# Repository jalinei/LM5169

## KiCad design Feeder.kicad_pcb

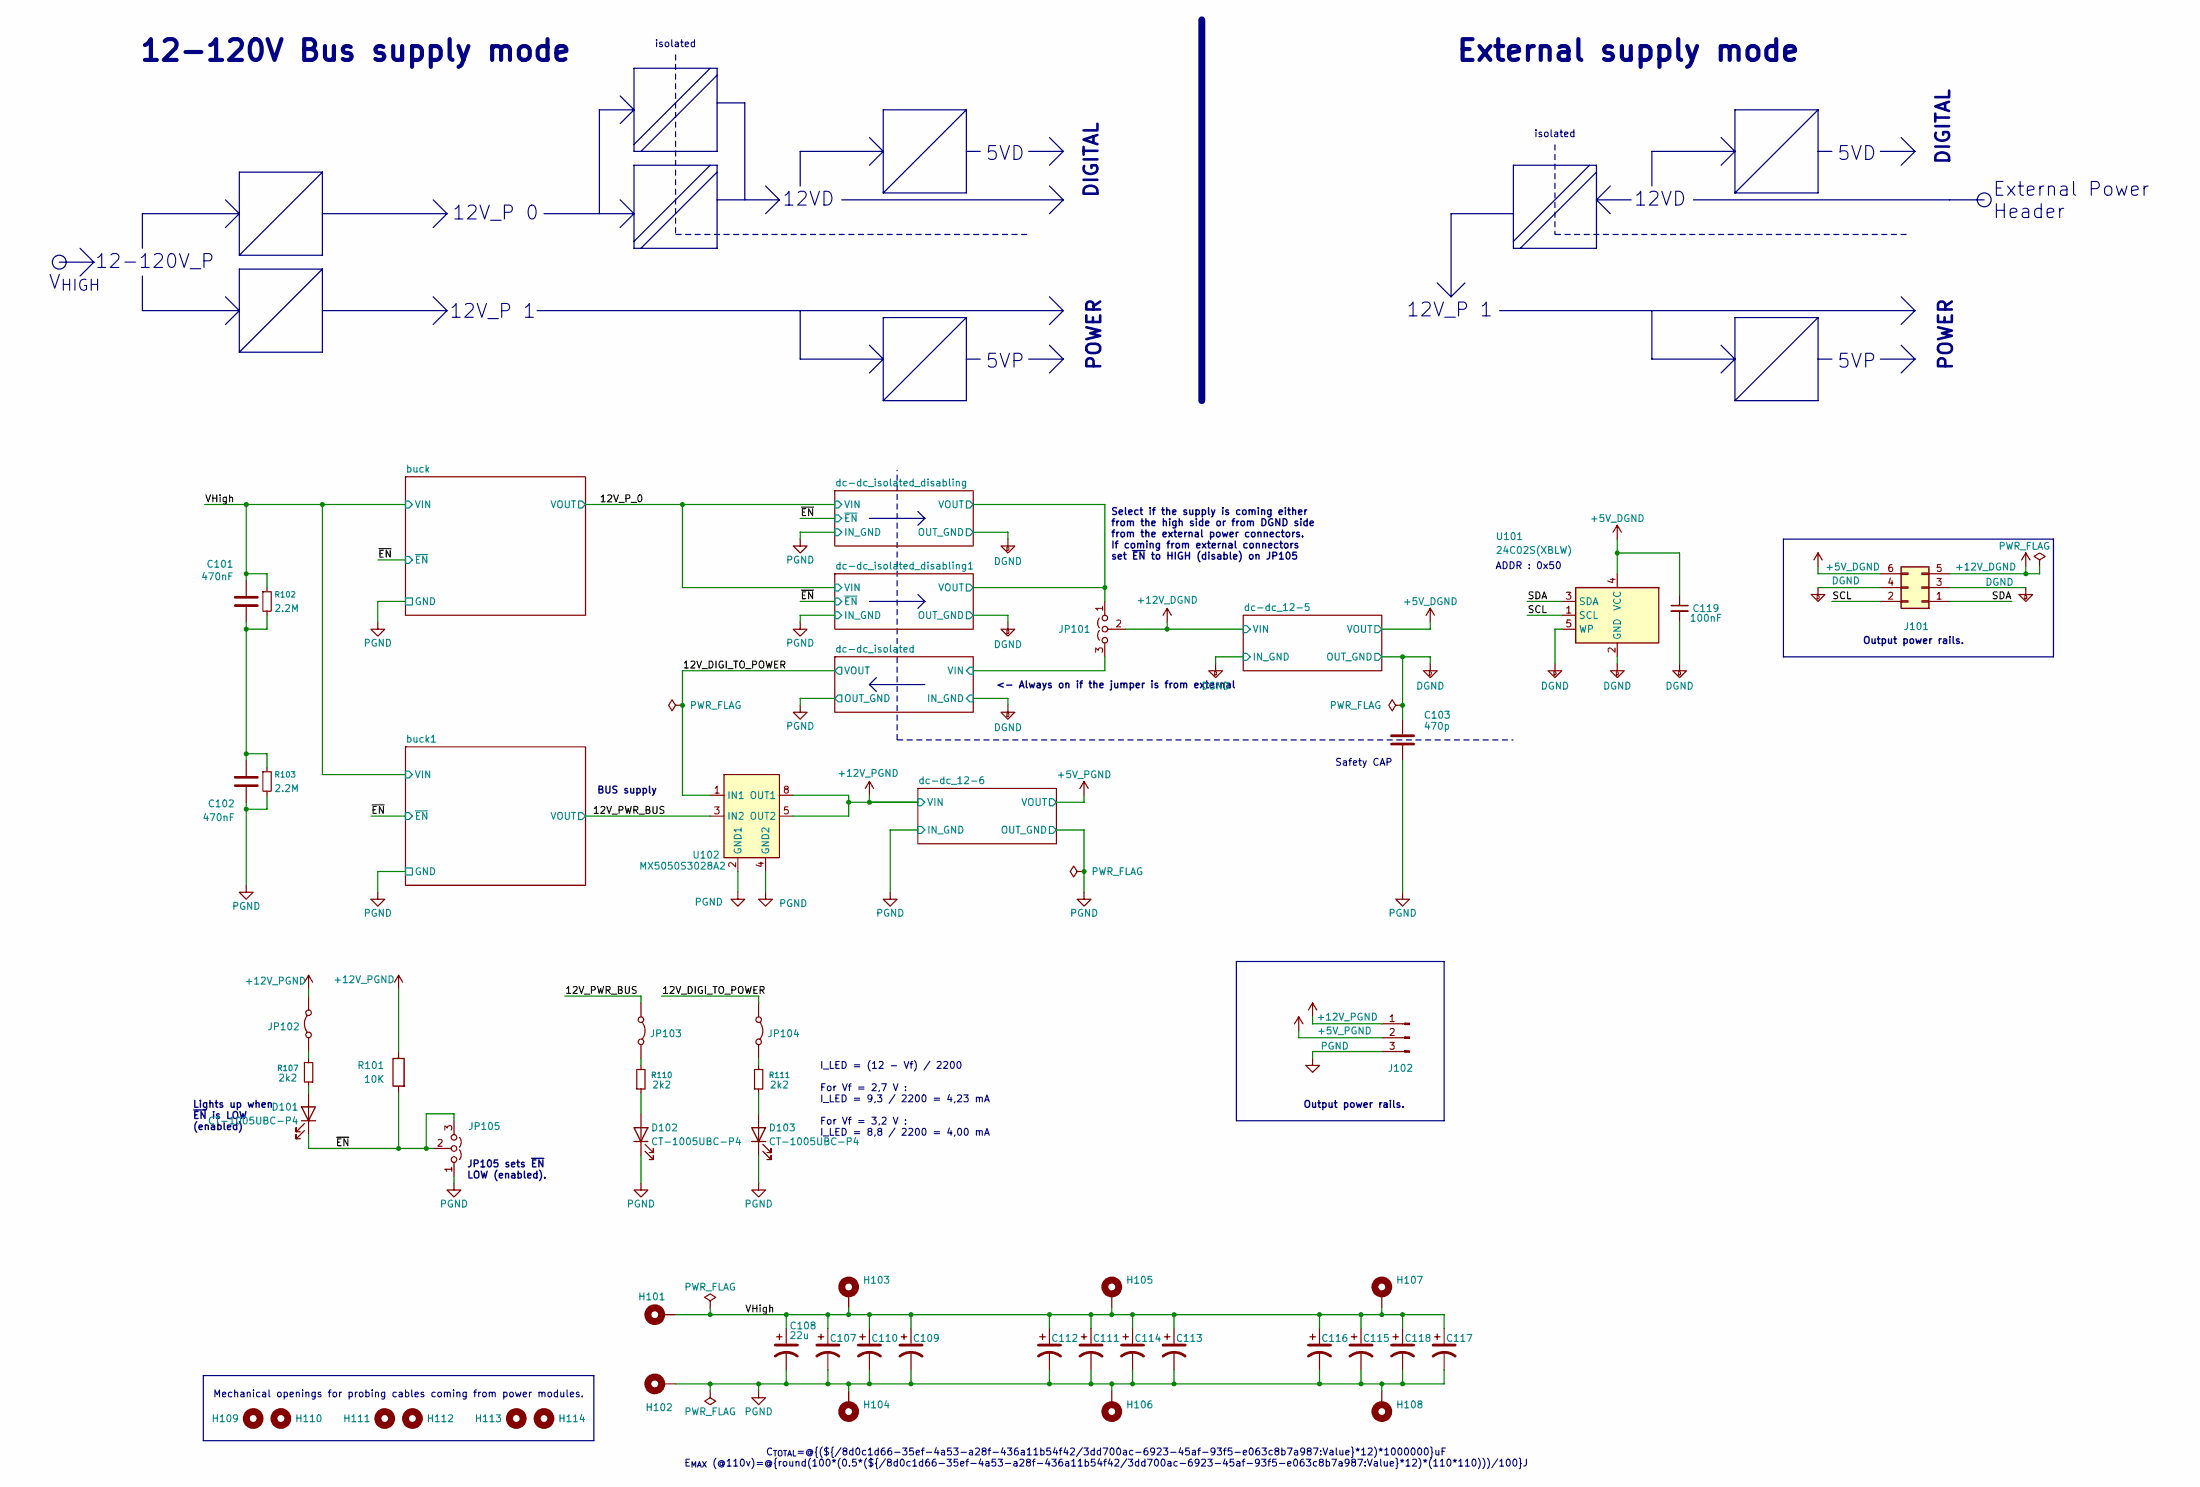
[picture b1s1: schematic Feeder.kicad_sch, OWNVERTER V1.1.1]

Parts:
C101, C102: 470nF; C_0805_2012Metric; LCSC C596323
C103: 470p; SAFETY_CAP_8.1x6mm; LCSC C20625786
C107, C108, C109, C110, C111, C112, C113, C114, C115, C116, C117, C118: 22u; CP_Elec_10x12.6; LCSC C487461
C119: 100nF; C_0603_1608Metric; LCSC C14663
D101, D102, D103: CT-1005UBC-P4; LED_0402_1005Metric; LCSC C52675962
H101, H102, H103, H104, H105, H106, H107, H108: MountingHole_Pad; MountingHole_3.2mm_M3_Pad_Via
H109, H110, H111, H112, H113, H114: MountingHole; Hole_signal_bottom_board_lookup
J101: PZ254V-22-06-A60-1500; PinHeader_2x03_P2.54mm_Vertical; LCSC C49056253
J102: PZ254V-21-03-A60-1500; PinHeader_1x03_P2.54mm_Vertical; LCSC C46971097
JP101, JP105: Jumper_3_Open; PinHeader_1x03_P2.54mm_Vertical
JP102, JP103, JP104: Jumper_2_Bridged; SolderJumper-2_P1.3mm_Bridged_RoundedPad1.0x1.5mm
R101: 10K; R_0603_1608Metric; LCSC C25804
R102, R103: 2.2M; R_0603_1608Metric; LCSC C22356574
R107, R110, R111: 2k2; R_0402_1005Metric; LCSC C25879
U101: 24C02S(XBLW); SOT-23-5; LCSC C18723540
U102: MX5050S3028A2; SOIC-8_3.9x4.9mm_P1.27mm; LCSC C51892073

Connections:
+5V_DGND: C119.1, J101.6, U101.4 (VCC); also elsewhere on the board
+5V_PGND: J102.2; also elsewhere on the board
+12V_DGND: J101.5, JP101.2 (C); also elsewhere on the board
+12V_PGND: J102.1, JP102.1 (A), R101.1, U102.5 (OUT2), U102.6 (OUT2), U102.7 (OUT1), U102.8 (OUT1); also elsewhere on the board
/12V_DIGI_TO_POWER: JP104.1 (A), U102.1 (IN1); also elsewhere on the board
/12V_PWR_BUS: JP103.1 (A), U102.3 (IN2); also elsewhere on the board
/SCL: J101.2, U101.1 (SCL)
/SDA: J101.1, U101.3 (SDA)
/VHigh: C101.1, C107.1, C108.1, C109.1, C110.1, C111.1, C112.1, C113.1, C114.1, C115.1, C116.1, C117.1, C118.1, H101.1 (1_1), H103.1 (1_1), H105.1 (1_1), H107.1 (1_1), R102.1; also elsewhere on the board
/dc-dc_isolated/VIN: JP101.3 (B); also elsewhere on the board
/dc-dc_isolated_disabling/VOUT: JP101.1 (A); also elsewhere on the board
/~EN: D101.1 (K), JP105.2 (C), JP105.3 (B), R101.2; also elsewhere on the board
DGND: C103.2, C119.2, J101.3, J101.4, U101.2 (GND), U101.5 (WP); also elsewhere on the board
unnamed: C101.2, C102.1, R102.2, R103.1
unnamed: D101.2 (A), R107.1
unnamed: D102.2 (A), R110.1
unnamed: D103.2 (A), R111.1
unnamed: JP102.2 (B), R107.2
unnamed: JP103.2 (B), R110.2
unnamed: JP104.2 (B), R111.2
PGND: C102.2, C103.1, C107.2, C108.2, C109.2, C110.2, C111.2, C112.2, C113.2, C114.2, C115.2, C116.2, C117.2, C118.2, D102.1 (K), D103.1 (K), H102.1 (1_1), H104.1 (1_1), H106.1 (1_1), H108.1 (1_1), J102.3, JP105.1 (A), R103.2, U102.2 (GND1), U102.4 (GND2); also elsewhere on the board

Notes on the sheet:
POWER
12V_P 0
I_LED = (12 - Vf) / 2200 For Vf = 2,7 V : I_LED = 9,3 / 2200 = 4,23 mA For Vf = 3,2 V : I_LED = 8,8 / 2200 = 4,00 mA
isolated
BUS supply
<- Always on if the jumper is from external
Safety CAP
JP105 sets ~{EN} LOW (enabled).
C_{TOTAL}=@{(${/8d0c1d66-35ef-4a53-a28f-436a11b54f42/3dd700ac-6923-45af-93f5-e063c8b7a987:Value}*12)*1000000}uF E_{MAX} (@110v)=@{round(100*(0.5*(${/8d0c1d66-35ef-4a53-a28f-436a11b54f42/3dd700ac-6923-45af-93f5-e063c8b7a987:Value}*12)*(110*110)))/100}J
ADDR : 0x50
12V_P 1
12VD
External Power Header
DIGITAL
5VD
5VP
12-120V_P
Mechanical openings for probing cables coming from power modules.
Lights up when ~{EN} is LOW (enabled)
External supply mode
Output power rails.
12-120V Bus supply mode
V_{HIGH}
Select if the supply is coming either from the high side or from DGND side from the external power connectors. If coming from external connectors set ~{EN} to HIGH (disable) on JP105

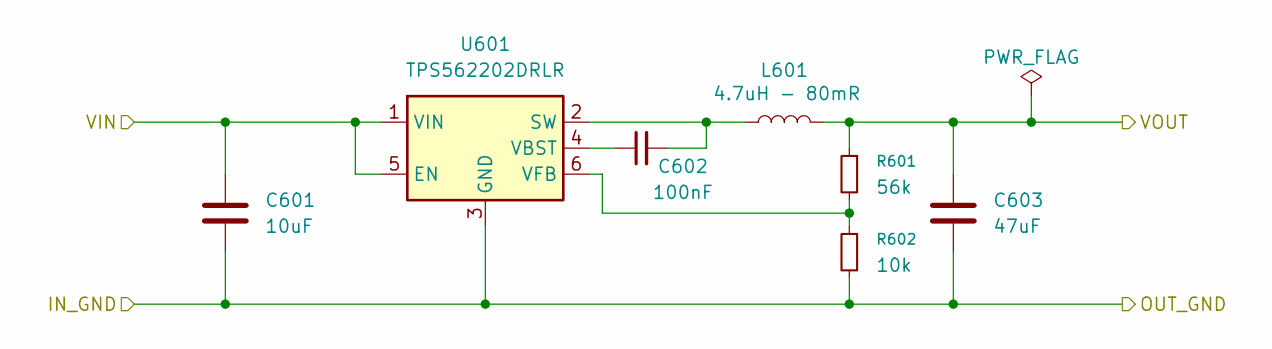
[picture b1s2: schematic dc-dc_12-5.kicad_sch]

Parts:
C601: 10uF; C_0805_2012Metric; LCSC C440198
C602: 100nF; C_0603_1608Metric; LCSC C14663
C603: 47uF; C_1206_3216Metric; LCSC C96123
L601: 4.7uH - 80mR; L_Cenker_CKCS4020; LCSC C3002596
R601: 56k; R_0603_1608Metric; LCSC C23206
R602: 10k; R_0603_1608Metric; LCSC C25804
U601: TPS562202DRLR; SOT-563; LCSC C2877547

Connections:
+5V_DGND: C603.1, L601.2, R601.1; also elsewhere on the board
+12V_DGND: C601.1, U601.1 (VIN), U601.5 (EN); also elsewhere on the board
DGND: C601.2, C603.2, R602.2, U601.3 (GND); also elsewhere on the board
unnamed: C602.2, L601.1, U601.2 (SW)
unnamed: C602.1, U601.4 (VBST)
unnamed: R601.2, R602.1, U601.6 (VFB)

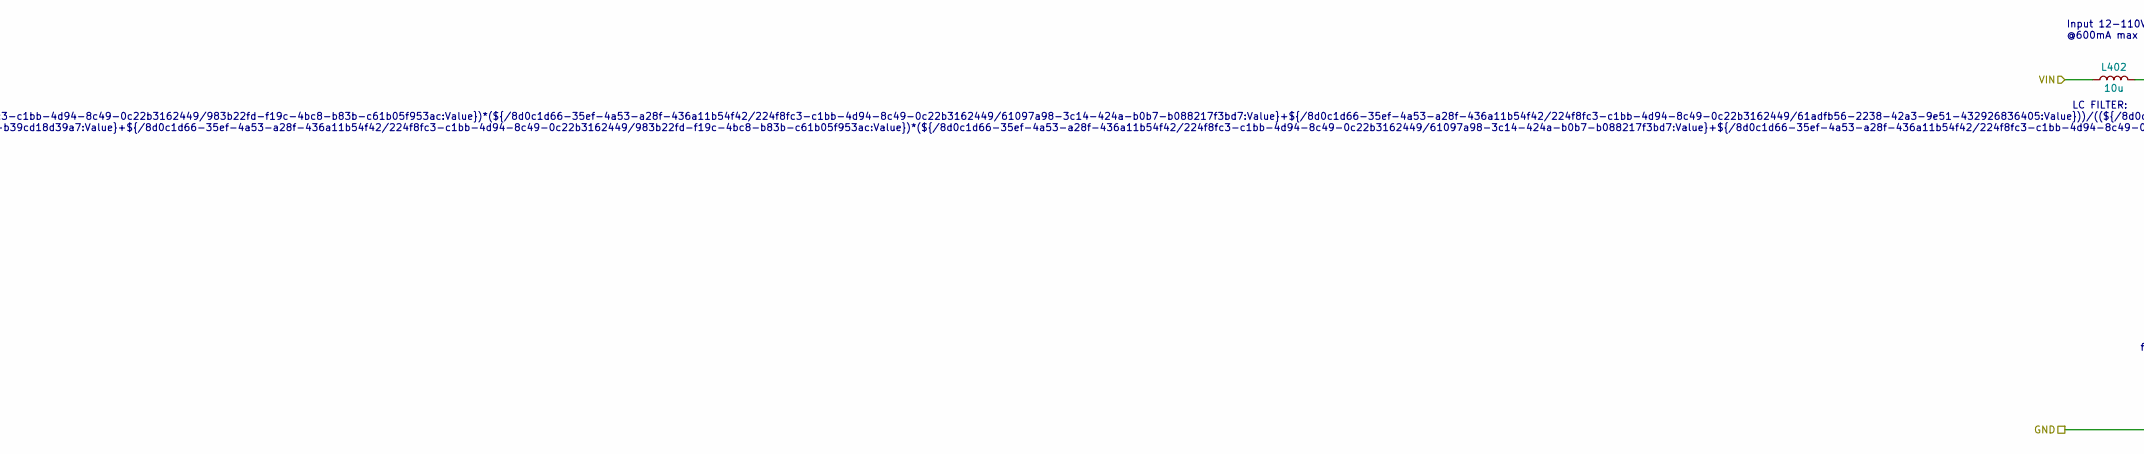
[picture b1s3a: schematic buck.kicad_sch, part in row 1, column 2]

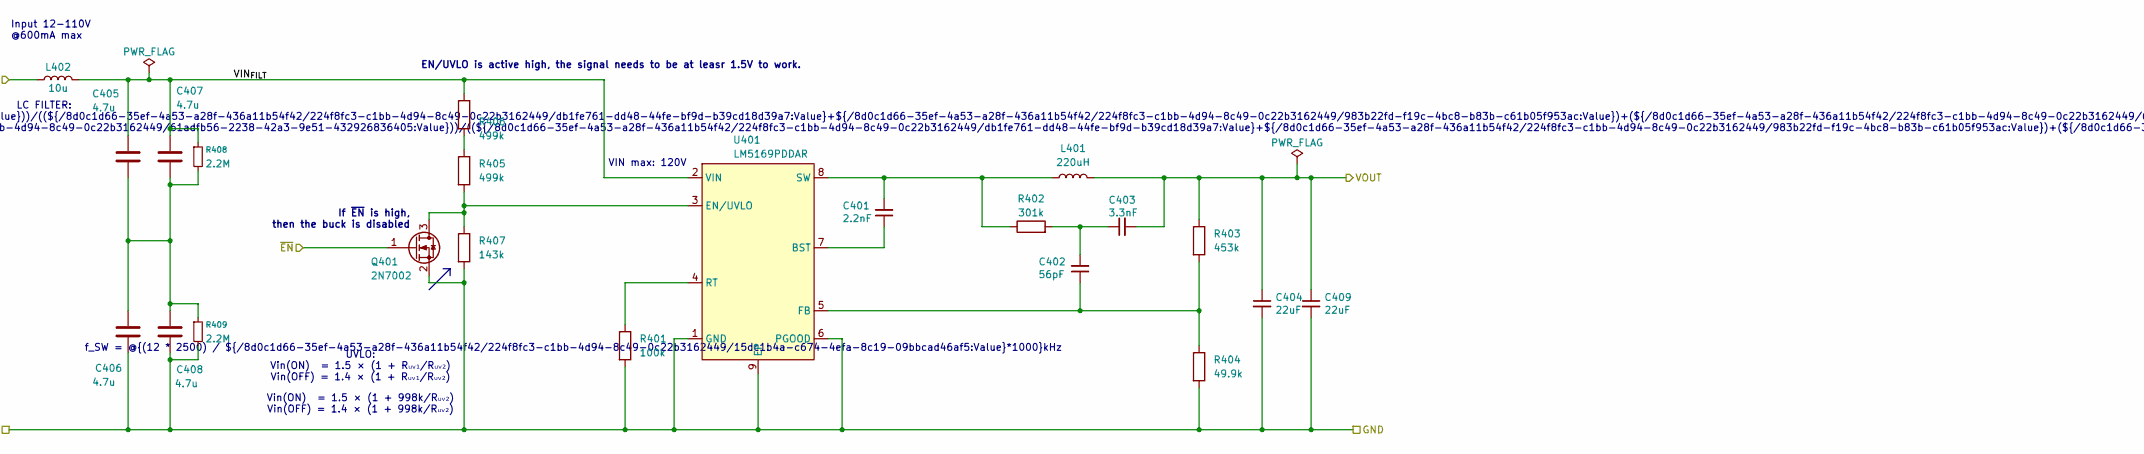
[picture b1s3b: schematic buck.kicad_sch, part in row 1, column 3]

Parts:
C401: 2.2nF; C_0805_2012Metric; LCSC C28260
C402: 56pF; C_0805_2012Metric; LCSC C1828
C403: 3.3nF; C_0805_2012Metric; LCSC C77062
C404, C409: 22uF; C_0805_2012Metric; LCSC C45783
C405, C406, C407, C408: 4.7u; C_1206_3216Metric; LCSC C22367839
L401: 220uH; L-SMD_L10.5-W10.3_SLD10D50; LCSC C216173
L402: 10u; L_Changjiang_FTC252008S; LCSC C46961986
Q401: 2N7002; SOT-23; LCSC C8545
R401: 100k; R_0603_1608Metric; LCSC C15458
R402: 301k; R_0805_2012Metric; LCSC C17619
R403: 453k; R_0805_2012Metric; LCSC C17702
R404: 49.9k; R_0805_2012Metric; LCSC C17719
R405, R406: 499k; R_0805_2012Metric; LCSC C17721
R407: 143k; R_0805_2012Metric; LCSC C247044
R408, R409: 2.2M; R_0603_1608Metric; LCSC C22356574
U401: LM5169PDDAR; Texas_R-PDSO-G8_EP2.95x4.9mm_Mask2.4x3.1mm_ThermalVias; LCSC C5439798

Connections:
/12V_P_0: C403.2, C404.1, C409.1, L401.2, R403.1; also elsewhere on the board
/VHigh: L402.1; also elsewhere on the board
/buck/VIN_{FILT}: C405.1, C407.1, L402.2, R406.1, R408.1, U401.2 (VIN)
/~EN: Q401.1 (G); also elsewhere on the board
unnamed: C402.2, C403.1, R402.2
unnamed: C405.2, C406.1, C407.2, C408.1, R408.2, R409.1
unnamed: Q401.3 (D), R405.2, R407.1, U401.3 (EN/UVLO)
unnamed: R405.1, R406.2
unnamed: C401.1, U401.7 (BST)
unnamed: C402.1, R403.2, R404.1, U401.5 (FB)
unnamed: R401.1, U401.4 (RT)
unnamed: C401.2, L401.1, R402.1, U401.8 (SW)
PGND: C404.2, C406.2, C408.2, C409.2, Q401.2 (S), R401.2, R404.2, R407.2, R409.2, U401.1 (GND), U401.6 (PGOOD), U401.9 (EP); also elsewhere on the board

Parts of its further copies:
C501: 2.2nF; C_0805_2012Metric; LCSC C28260
C502: 56pF; C_0805_2012Metric; LCSC C1828
C503: 3.3nF; C_0805_2012Metric; LCSC C77062
C504, C509: 22uF; C_0805_2012Metric; LCSC C45783
C505, C506, C507, C508: 4.7u; C_1206_3216Metric; LCSC C22367839
L501: 220uH; L-SMD_L10.5-W10.3_SLD10D50; LCSC C216173
L502: 10u; L_Changjiang_FTC252008S; LCSC C46961986
Q501: 2N7002; SOT-23; LCSC C8545
R501: 100k; R_0603_1608Metric; LCSC C15458
R502: 301k; R_0805_2012Metric; LCSC C17619
R503: 453k; R_0805_2012Metric; LCSC C17702
R504: 49.9k; R_0805_2012Metric; LCSC C17719
R505, R506: 499k; R_0805_2012Metric; LCSC C17721
R507: 143k; R_0805_2012Metric; LCSC C247044
R508, R509: 2.2M; R_0603_1608Metric; LCSC C22356574
U501: LM5169PDDAR; Texas_R-PDSO-G8_EP2.95x4.9mm_Mask2.4x3.1mm_ThermalVias; LCSC C5439798

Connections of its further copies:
/12V_PWR_BUS: C503.2, C504.1, C509.1, L501.2, R503.1; also elsewhere on the board
/VHigh: L502.1; also elsewhere on the board
/buck1/VIN_{FILT}: C505.1, C507.1, L502.2, R506.1, R508.1, U501.2 (VIN)
/~EN: Q501.1 (G); also elsewhere on the board
unnamed: C502.2, C503.1, R502.2
unnamed: C505.2, C506.1, C507.2, C508.1, R508.2, R509.1
unnamed: Q501.3 (D), R505.2, R507.1, U501.3 (EN/UVLO)
unnamed: R505.1, R506.2
unnamed: C501.1, U501.7 (BST)
unnamed: C502.1, R503.2, R504.1, U501.5 (FB)
unnamed: R501.1, U501.4 (RT)
unnamed: C501.2, L501.1, R502.1, U501.8 (SW)
PGND: C504.2, C506.2, C508.2, C509.2, Q501.2 (S), R501.2, R504.2, R507.2, R509.2, U501.1 (GND), U501.6 (PGOOD), U501.9 (EP); also elsewhere on the board

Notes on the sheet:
Input 12-110V @600mA max
Vin(ON) = 1.5 × (1 + 998k/Rᵤᵥ₂) Vin(OFF) = 1.4 × (1 + 998k/Rᵤᵥ₂)
If ~{EN} is high, then the buck is disabled
VIN max: 120V
LC FILTER: Ceq = @{((${/8d0c1d66-35ef-4a53-a28f-436a11b54f42/224f8fc3-c1bb-4d94-8c49-0c22b3162449/db1fe761-dd48-44fe-bf9d-b39cd18d39a7:Value}+${/8d0c1d66-35ef-4a53-a28f-436a11b54f42/224f8fc3-c1bb-4d94-8c49-0c22b3162449/983b22fd-f19c-4bc8-b83b-c61b05f953ac:Value})*(${/8d0c1d66-35ef-4a53-a28f-436a11b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
EN/UVLO is active high, the signal needs to be at leasr 1.5V to work.
UVLO: Vin(ON) = 1.5 × (1 + Rᵤᵥ₁/Rᵤᵥ₂) Vin(OFF) = 1.4 × (1 + Rᵤᵥ₁/Rᵤᵥ₂)
f_SW = @{(12 * 2500) / ${/8d0c1d66-35ef-4a53-a28f-436a11b54f42/224f8fc3-c1bb-4d94-8c49-0c22b3162449/15dc1b4a-c674-4efa-8c19-09bbcad46af5:Value}*1000}kHz

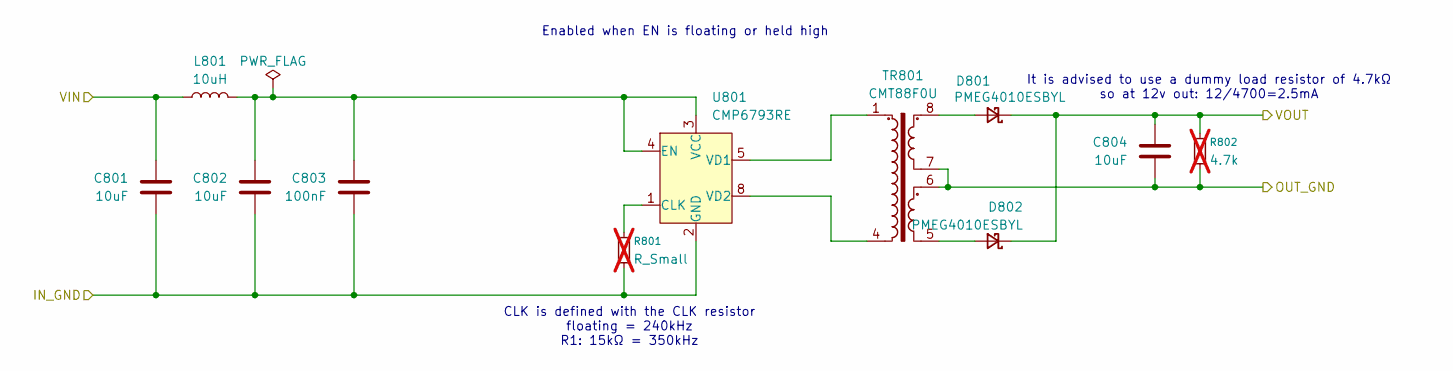
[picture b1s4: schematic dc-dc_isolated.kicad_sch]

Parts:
C801, C802, C804: 10uF; C_0805_2012Metric; LCSC C440198
C803: 100nF; C_0603_1608Metric; LCSC C14663
D801, D802: PMEG4010ESBYL; D_SOD-882; LCSC C478156
L801: 10uH; L_0805_2012Metric; LCSC C88173
R801: R_Small; R_0603_1608Metric; not fitted
R802: 4.7k; R_0603_1608Metric; not fitted
TR801: CMT88F0U; LCSC C37648313
U801: CMP6793RE; SOIC-8-1EP_3.9x4.9mm_P1.27mm_EP2.41x3.3mm_ThermalVias; LCSC C47117018

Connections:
/12V_DIGI_TO_POWER: C804.1, D801.1 (K), D802.1 (K), R802.1; also elsewhere on the board
/dc-dc_isolated/VIN: C801.1, L801.1; also elsewhere on the board
DGND: C801.2, C802.2, C803.2, R801.2, U801.2 (GND), U801.9 (GND); also elsewhere on the board
unnamed: D801.2 (A), TR801.8
unnamed: D802.2 (A), TR801.5
unnamed: R801.1, U801.1 (CLK)
unnamed: C802.1, C803.1, L801.2, U801.3 (VCC), U801.4 (EN)
unnamed: TR801.1, U801.5 (VD1)
unnamed: TR801.4, U801.8 (VD2)
PGND: C804.2, R802.2, TR801.6, TR801.7; also elsewhere on the board

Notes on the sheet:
It is advised to use a dummy load resistor of 4.7kΩ so at 12v out: 12/4700=2.5mA
Enabled when EN is floating or held high
CLK is defined with the CLK resistor floating = 240kHz R1: 15kΩ = 350kHz

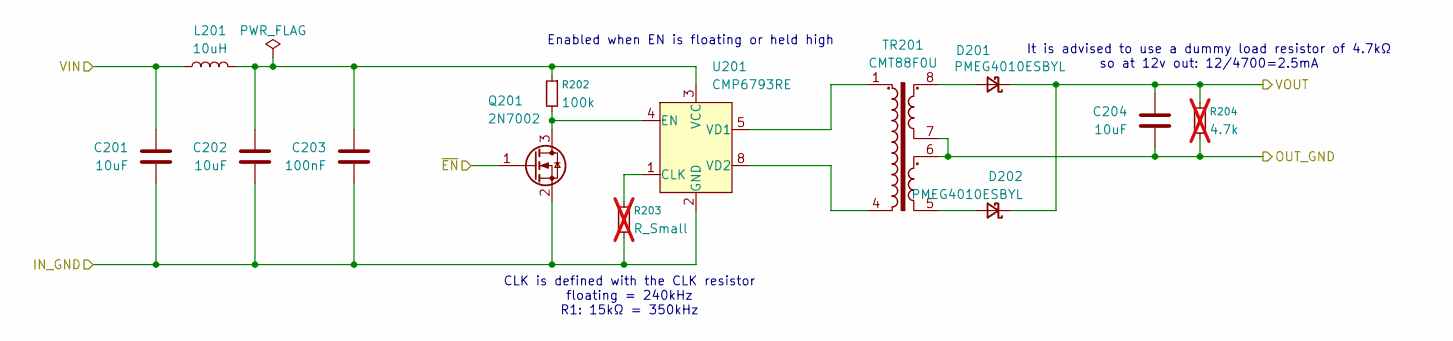
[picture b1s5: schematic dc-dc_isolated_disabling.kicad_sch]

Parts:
C201, C202, C204: 10uF; C_0805_2012Metric; LCSC C440198
C203: 100nF; C_0603_1608Metric; LCSC C14663
D201, D202: PMEG4010ESBYL; D_SOD-882; LCSC C478156
L201: 10uH; L_0805_2012Metric; LCSC C88173
Q201: 2N7002; SOT-23; LCSC C8545
R202: 100k; R_0603_1608Metric; LCSC C15458
R203: R_Small; R_0603_1608Metric; not fitted
R204: 4.7k; R_0603_1608Metric; not fitted
TR201: CMT88F0U; LCSC C37648313
U201: CMP6793RE; SOIC-8-1EP_3.9x4.9mm_P1.27mm_EP2.41x3.3mm_ThermalVias; LCSC C47117018

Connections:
/12V_P_0: C201.1, L201.1; also elsewhere on the board
/dc-dc_isolated_disabling/VOUT: C204.1, D201.1 (K), D202.1 (K), R204.1; also elsewhere on the board
/~EN: Q201.1 (G); also elsewhere on the board
DGND: C204.2, R204.2, TR201.6, TR201.7; also elsewhere on the board
unnamed: D201.2 (A), TR201.8
unnamed: D202.2 (A), TR201.5
unnamed: Q201.3 (D), R202.2, U201.4 (EN)
unnamed: R203.1, U201.1 (CLK)
unnamed: C202.1, C203.1, L201.2, R202.1, U201.3 (VCC)
unnamed: TR201.1, U201.5 (VD1)
unnamed: TR201.4, U201.8 (VD2)
PGND: C201.2, C202.2, C203.2, Q201.2 (S), R203.2, U201.2 (GND), U201.9 (GND); also elsewhere on the board

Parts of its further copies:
C301, C302, C304: 10uF; C_0805_2012Metric; LCSC C440198
C303: 100nF; C_0603_1608Metric; LCSC C14663
D301, D302: PMEG4010ESBYL; D_SOD-882; LCSC C478156
L301: 10uH; L_0805_2012Metric; LCSC C88173
Q301: 2N7002; SOT-23; LCSC C8545
R302: 100k; R_0603_1608Metric; LCSC C15458
R303: R_Small; R_0603_1608Metric; not fitted
R304: 4.7k; R_0603_1608Metric; not fitted
TR301: CMT88F0U; LCSC C37648313
U301: CMP6793RE; SOIC-8-1EP_3.9x4.9mm_P1.27mm_EP2.41x3.3mm_ThermalVias; LCSC C47117018

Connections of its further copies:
/12V_P_0: C301.1, L301.1; also elsewhere on the board
/dc-dc_isolated_disabling/VOUT: C304.1, D301.1 (K), D302.1 (K), R304.1; also elsewhere on the board
/~EN: Q301.1 (G); also elsewhere on the board
DGND: C304.2, R304.2, TR301.6, TR301.7; also elsewhere on the board
unnamed: D301.2 (A), TR301.8
unnamed: D302.2 (A), TR301.5
unnamed: Q301.3 (D), R302.2, U301.4 (EN)
unnamed: R303.1, U301.1 (CLK)
unnamed: C302.1, C303.1, L301.2, R302.1, U301.3 (VCC)
unnamed: TR301.1, U301.5 (VD1)
unnamed: TR301.4, U301.8 (VD2)
PGND: C301.2, C302.2, C303.2, Q301.2 (S), R303.2, U301.2 (GND), U301.9 (GND); also elsewhere on the board

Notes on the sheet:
Enabled when EN is floating or held high
CLK is defined with the CLK resistor floating = 240kHz R1: 15kΩ = 350kHz
It is advised to use a dummy load resistor of 4.7kΩ so at 12v out: 12/4700=2.5mA

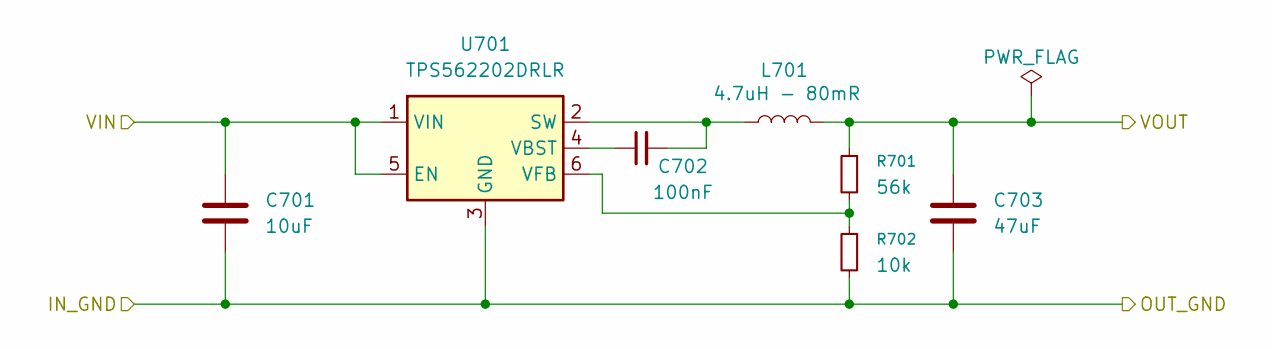
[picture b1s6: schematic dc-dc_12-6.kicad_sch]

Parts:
C701: 10uF; C_0805_2012Metric; LCSC C440198
C702: 100nF; C_0603_1608Metric; LCSC C14663
C703: 47uF; C_1206_3216Metric; LCSC C96123
L701: 4.7uH - 80mR; L_Cenker_CKCS4020; LCSC C3002596
R701: 56k; R_0603_1608Metric; LCSC C23206
R702: 10k; R_0603_1608Metric; LCSC C25804
U701: TPS562202DRLR; SOT-563; LCSC C2877547

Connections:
+5V_PGND: C703.1, L701.2, R701.1; also elsewhere on the board
+12V_PGND: C701.1, U701.1 (VIN), U701.5 (EN); also elsewhere on the board
unnamed: C702.2, L701.1, U701.2 (SW)
unnamed: C702.1, U701.4 (VBST)
unnamed: R701.2, R702.1, U701.6 (VFB)
PGND: C701.2, C703.2, R702.2, U701.3 (GND); also elsewhere on the board

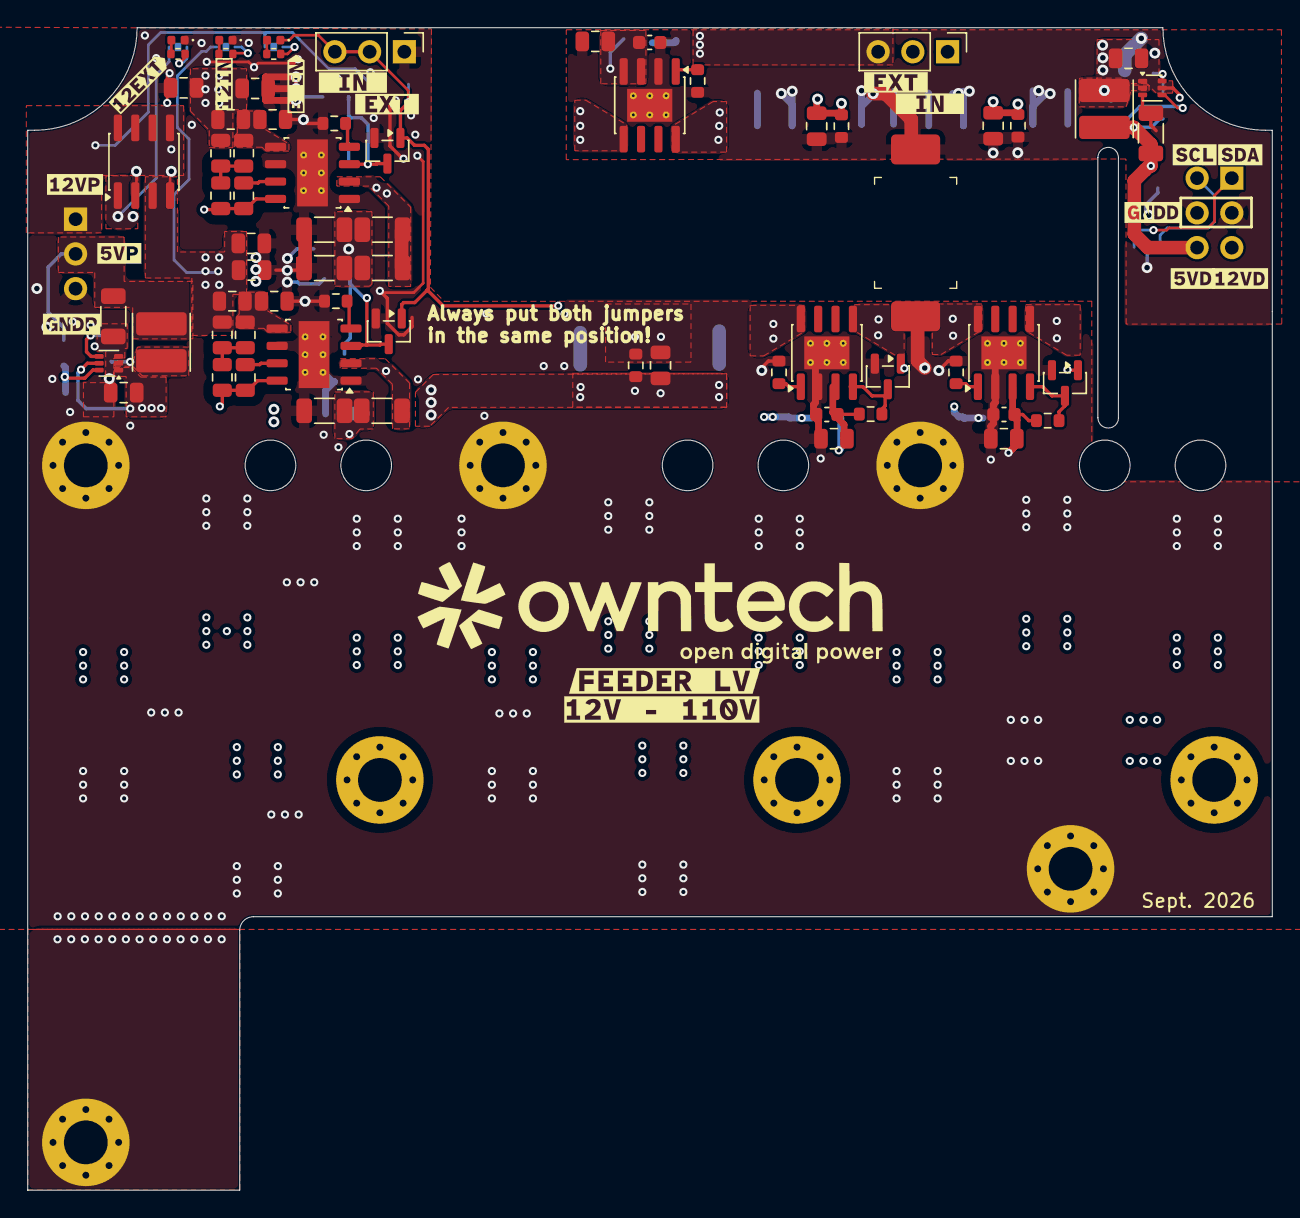
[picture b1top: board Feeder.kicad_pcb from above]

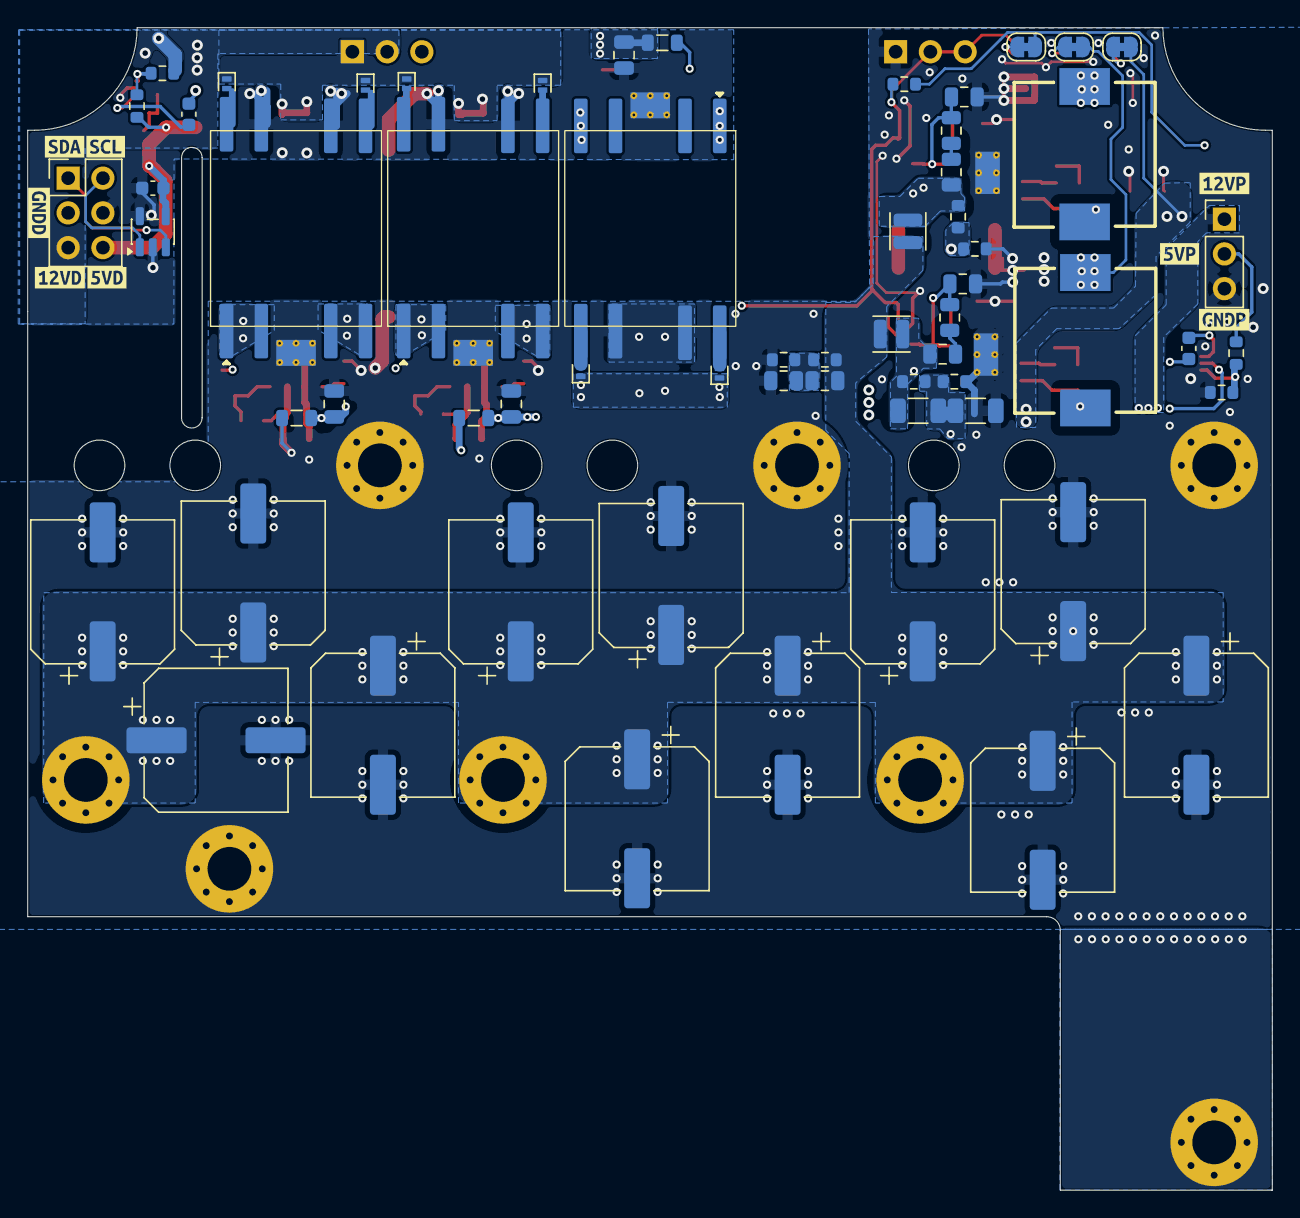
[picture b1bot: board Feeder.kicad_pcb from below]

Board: 4 copper layers, 91.0 x 85.0 mm, 168 parts (69 on the bottom side), 66 nets.

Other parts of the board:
kibuzzard-6A7463BC: G***; kibuzzard-6A7463BC
kibuzzard-6A74635F: G***; kibuzzard-6A74635F
kibuzzard-6A74639F: G***; kibuzzard-6A74639F
kibuzzard-6A746332: G***; kibuzzard-6A746332
kibuzzard-6A746339: G***; kibuzzard-6A746339
kibuzzard-6A746342: G***; kibuzzard-6A746342
kibuzzard-6A746363: G***; kibuzzard-6A746363
kibuzzard-6A746399: G***; kibuzzard-6A746399
kibuzzard-6AA2B6A2: G***; kibuzzard-6AA2B6A2
kibuzzard-6AA2B6A7: G***; kibuzzard-6AA2B6A7
kibuzzard-6AA2B6AD: G***; kibuzzard-6AA2B6AD
kibuzzard-6AA2B6B2: G***; kibuzzard-6AA2B6B2
kibuzzard-6AA2B6BA: G***; kibuzzard-6AA2B6BA
kibuzzard-6AA2B6C2: G***; kibuzzard-6AA2B6C2
kibuzzard-6AA2B6CC: G***; kibuzzard-6AA2B6CC
kibuzzard-6AA2B6DD: G***; kibuzzard-6AA2B6DD
kibuzzard-6AA2B6E1: G***; kibuzzard-6AA2B6E1
kibuzzard-6AA2B6E8: G***; kibuzzard-6AA2B6E8
kibuzzard-6AA2B66E: G***; kibuzzard-6AA2B66E
kibuzzard-6AA2B68C: G***; kibuzzard-6AA2B68C
kibuzzard-6AA2B679: G***; kibuzzard-6AA2B679
kibuzzard-6AA2B681: G***; kibuzzard-6AA2B681
kibuzzard-6AA2B687: G***; kibuzzard-6AA2B687
kibuzzard-6AA2B692: G***; kibuzzard-6AA2B692
kibuzzard-6AA2B784: G***; kibuzzard-6AA2B784
